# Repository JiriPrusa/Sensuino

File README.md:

Sensuino
========

Welcome on Sensuino project repository!

Here you can find schemats for Sensuino shield, EC modul and pH modul in folder Schema. Also the Arduino code for Sensunino shield and relevant libraries are placed here in folder Arduino. And at last source code in JAVA for SensApl application is situated in folder SensApl.

=======

More information about project can be found on project page : http://sensuino.net

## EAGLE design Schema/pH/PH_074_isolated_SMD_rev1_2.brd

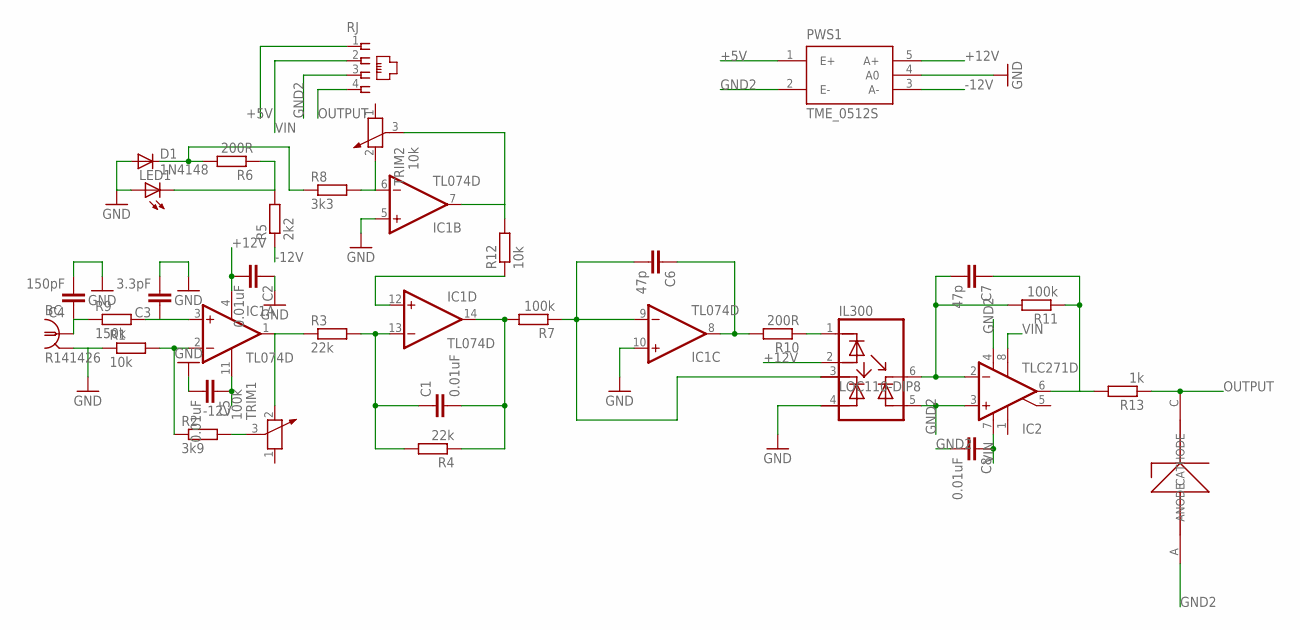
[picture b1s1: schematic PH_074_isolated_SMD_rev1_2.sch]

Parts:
BC: R141426
C1, C2: 0.01uF; C1206
C3: 3.3pF; C0805
C4: 150pF; C0805
C5, C8: 0.01uF; C0805
C6: 47p; C0805
C7: 47p; C1206
D1: 1N4148; R1206W
IC1: TL074D; SO14
IC2: TLC271D; SO08
IL300: LOC110-DIP8; DIP8
LED1: LED3MM
PWS1: TME_0512S; TMEXXXXS
R1, R12: 10k; R1206W
R2: 3k9; R1206W
R3, R4: 22k; R1206W
R5: 2k2; R1206W
R6, R10: 200R; R1206W
R7, R11: 100k; R1206W
R8: 3k3; R1206W
R9: 150k; R0805W
R13: 1k; R1206W
RJ: 14867
TRIM1: 100k; PT-10
TRIM2: 10k; PT-10
U$1: ZENER; SOD80-W

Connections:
+5V: PWS1.1 (E+), RJ.1
+12V: C2.2, IC1.4 (V+), IL300.2, PWS1.5 (A+)
-12V: C5.1, IC1.11 (V-), PWS1.3 (A-), R5.1
GND: BC.2 (GND), BC.3 (GND), BC.4 (GND), BC.5 (GND), C2.1, C3.2, C4.2, C5.2, D1.1 (A), IC1.5 (+IN), IC1.10 (+IN), IL300.4, LED1.A, PWS1.4 (A0), R1.1
GND2: C8.2, IC2.3 (+IN), IC2.4 (V-), IL300.5, PWS1.2 (E-), RJ.3, U$1.A (ANODE)
IN: C1.2, IC1.14 (OUT), R4.1, R7.2
unnamed: IC1.6 (-IN), R8.2, TRIM2.2
unnamed: IC1.2 (-IN), R1.2, R2.1
unnamed: C3.1, IC1.3 (+IN), R9.2
unnamed: C6.2, IC1.9 (-IN), IL300.3, R7.1
unnamed: R2.2, TRIM1.3
unnamed: BC.1, C4.1, R9.1
unnamed: D1.2 (C), R6.2, R8.1
unnamed: LED1.K (C), R5.2, R6.1
unnamed: IL300.1, R10.1
unnamed: IC1.7 (OUT), R12.2, TRIM2.3
unnamed: IC1.1 (OUT), R3.1, TRIM1.2
unnamed: C6.1, IC1.8 (OUT), R10.2
unnamed: IC1.12 (+IN), R12.1
unnamed: C1.1, IC1.13 (-IN), R3.2, R4.2
unnamed: C7.2, IC2.2 (-IN), IL300.6, R11.2
NIC: C7.1, IC2.6 (OUT), R11.1, R13.2
OUTPUT: R13.1, RJ.4, U$1.C (CATHODE)
VIN: C8.1, IC2.7 (V+), IC2.8 (OPT), RJ.2

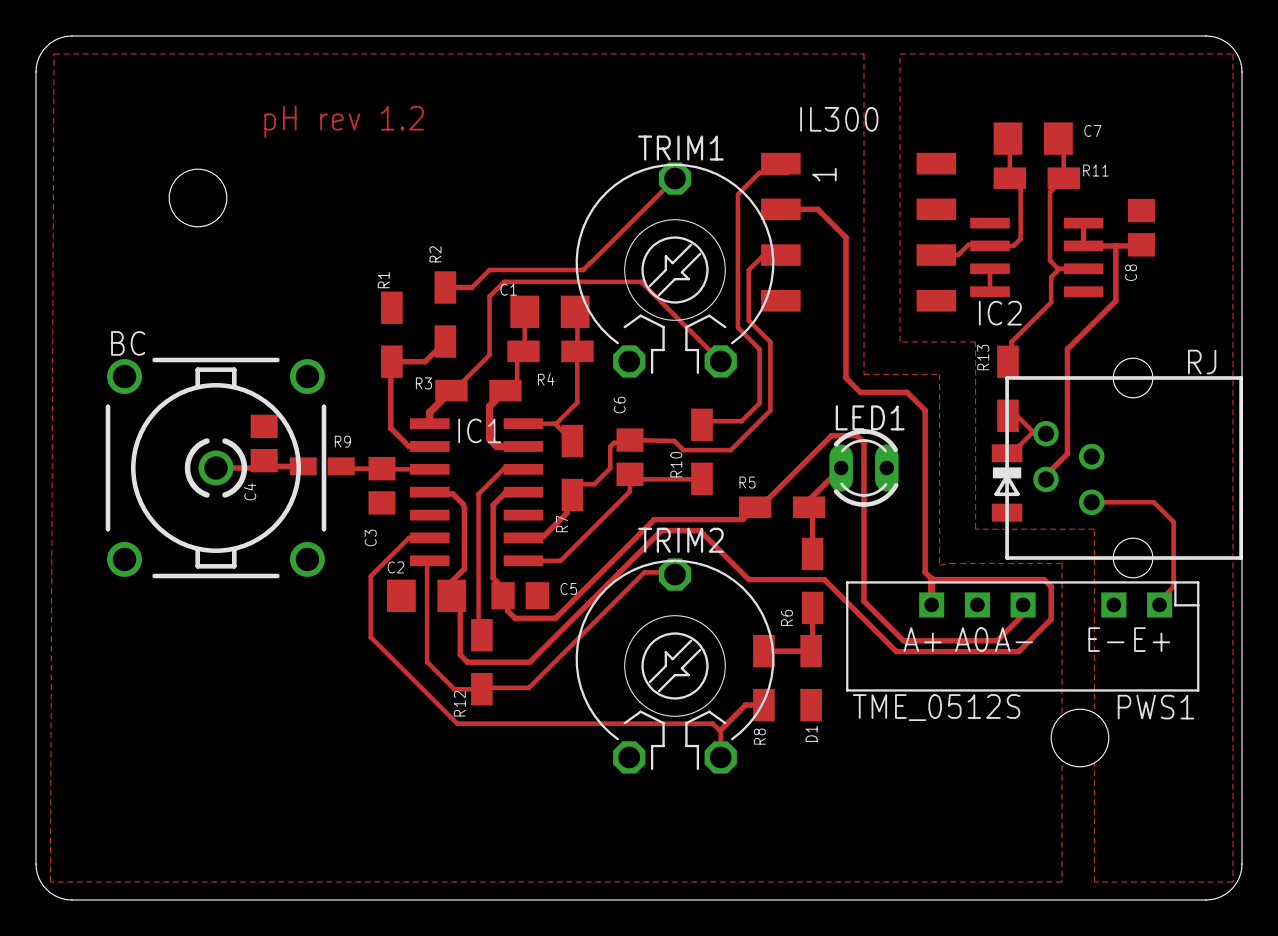
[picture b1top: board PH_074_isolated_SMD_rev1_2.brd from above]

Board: 2 copper layers, 67.0 x 48.0 mm, 32 parts (0 on the bottom side), 24 nets.

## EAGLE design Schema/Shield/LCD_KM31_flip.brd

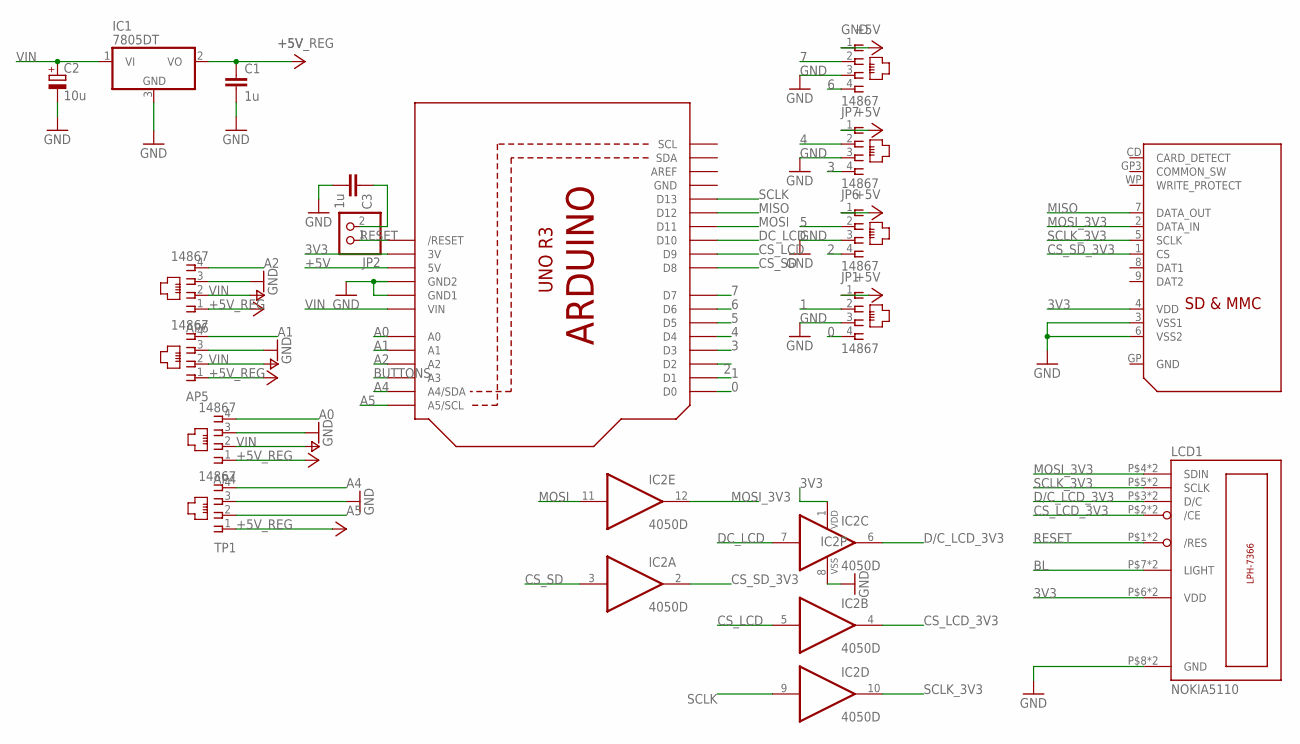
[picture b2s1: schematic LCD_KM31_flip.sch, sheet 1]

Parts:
AP4, AP5, AP6: 14867
C1, C3: 1u; C1206
C2: 10u; SMC_C
GND: 14867
IC1: 7805DT; TO252
IC2: 4050D; SO16
JP1, JP6, JP7: 14867
JP2: PINHD-1X2; 1X02
LCD1: NOKIA5110; LPH-7366
TP1: 14867
U$1: ARDUINOR3-NOIOREF-NOTEXT; ARDUINOR3-NOTEXT-NOIOREF
U$2: SDMMC06132; 06132

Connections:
0: JP1.4, U$1.D0
1: JP1.2, U$1.D1
2: JP6.4, U$1.D2
3: JP7.4, U$1.D3
3V3: IC2.1 (VDD), LCD1.P$6 (VDD), LCD1.P$14 (VDD), U$1.3V, U$2.4 (VDD)
4: JP7.2, U$1.D4
5: JP6.2, U$1.D5
6: GND.4, U$1.D6
7: GND.2, U$1.D7
+5V: GND.1, JP1.1, JP6.1, JP7.1, U$1.5V; also elsewhere on the board
+5V_REG: AP4.1, AP5.1, AP6.1, C1.1, IC1.2 (VO), TP1.1
A0: AP4.4, U$1.A0
A1: AP5.4, U$1.A1
A2: AP6.4, U$1.A2
A4: TP1.4, U$1.A4 (A4/SDA)
A5: TP1.2, U$1.A5 (A5/SCL)
BL: LCD1.P$7 (LIGHT), LCD1.P$15 (LIGHT); also elsewhere on the board
BUTTONS: U$1.A3; also elsewhere on the board
CS_LCD: IC2.5 (I), U$1.D9
CS_LCD_3V3: IC2.4 (O), LCD1.P$2 (/CE), LCD1.P$10 (/CE)
CS_SD: IC2.3 (I), U$1.D8
CS_SD_3V3: IC2.2 (O), U$2.1 (CS)
D/C_LCD_3V3: IC2.6 (O), LCD1.P$3 (D/C), LCD1.P$11 (D/C)
DC_LCD: IC2.7 (I), U$1.D10
GND: AP4.3, AP5.3, AP6.3, C1.2, C2.-, C3.2, GND.3, IC1.3 (GND), IC2.8 (VSS), JP1.3, JP6.3, JP7.3, LCD1.P$8 (GND), LCD1.P$16 (GND), TP1.3, U$1.GND, U$1.GND1, U$1.GND2, U$2.3 (VSS1), U$2.6 (VSS2); also elsewhere on the board
MISO: U$1.D12, U$2.7 (DATA_OUT)
MOSI: IC2.11 (I), U$1.D11
MOSI_3V3: IC2.12 (O), LCD1.P$4 (SDIN), LCD1.P$12 (SDIN), U$2.2 (DATA_IN)
unnamed: C3.1, JP2.2
RESET: JP2.1, LCD1.P$1 (/RES), LCD1.P$9 (/RES), U$1.RESET (/RESET)
SCLK: IC2.9 (I), U$1.D13
SCLK_3V3: IC2.10 (O), LCD1.P$5 (SCLK), LCD1.P$13 (SCLK), U$2.5 (SCLK)
VIN: AP4.2, AP5.2, AP6.2, C2.+, IC1.1 (VI), U$1.VIN

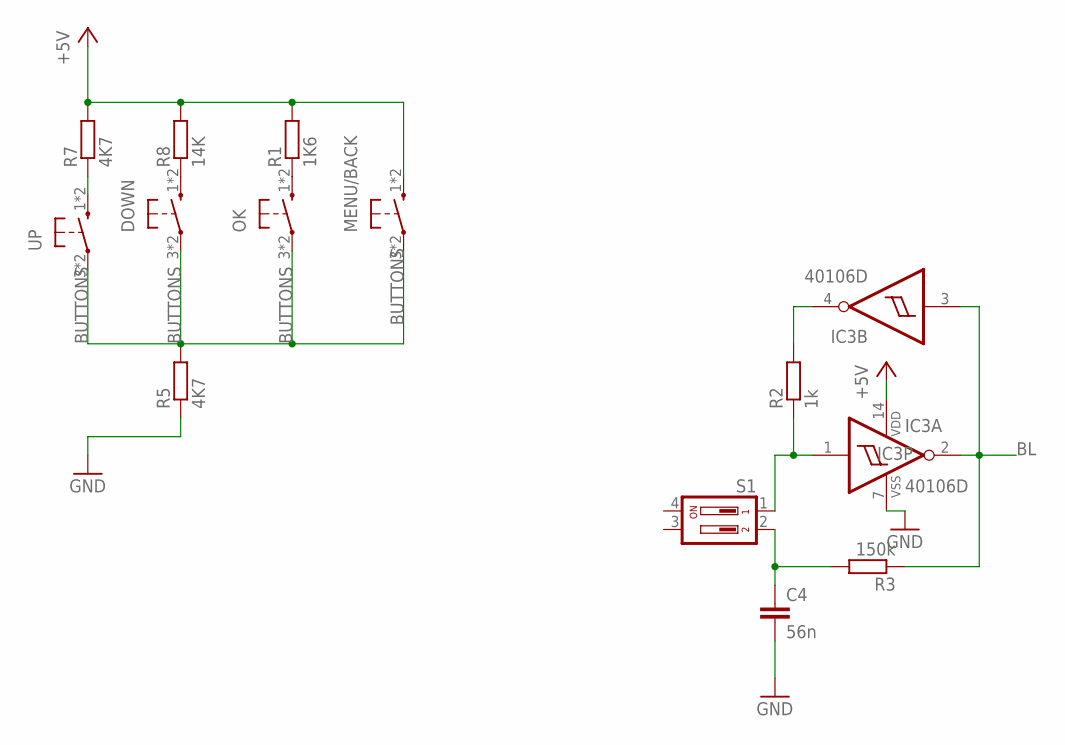
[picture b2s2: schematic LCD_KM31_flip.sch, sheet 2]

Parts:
C4: 56n; C0805
DOWN: 10-XX; B3F-10XX
IC3: 40106D; SO14
MENU/BACK: 10-XX; B3F-10XX
OK: 10-XX; B3F-10XX
R1: 1K6; M0805
R2: 1k; R0805W
R3: 150k; R0805W
R5, R7: 4K7; M0805
R8: 14K; M0805
S1: SD4-02
UP: 10-XX; B3F-10XX

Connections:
+5V: IC3.14 (VDD), MENU/BACK.1 (S), MENU/BACK.2 (S), R1.2, R7.2, R8.2; also elsewhere on the board
BL: IC3.2 (O), IC3.3 (I), R3.1; also elsewhere on the board
BUTTONS: DOWN.3, DOWN.4, MENU/BACK.3, MENU/BACK.4, OK.3, OK.4, R5.2, UP.3, UP.4; also elsewhere on the board
GND: C4.2, IC3.7 (VSS), R5.1; also elsewhere on the board
unnamed: DOWN.1 (S), DOWN.2 (S), R8.1
unnamed: OK.1 (S), OK.2 (S), R1.1
unnamed: R7.1, UP.1 (S), UP.2 (S)
unnamed: C4.1, R3.2, S1.2
unnamed: IC3.1 (I), R2.1, S1.1
unnamed: IC3.4 (O), R2.2

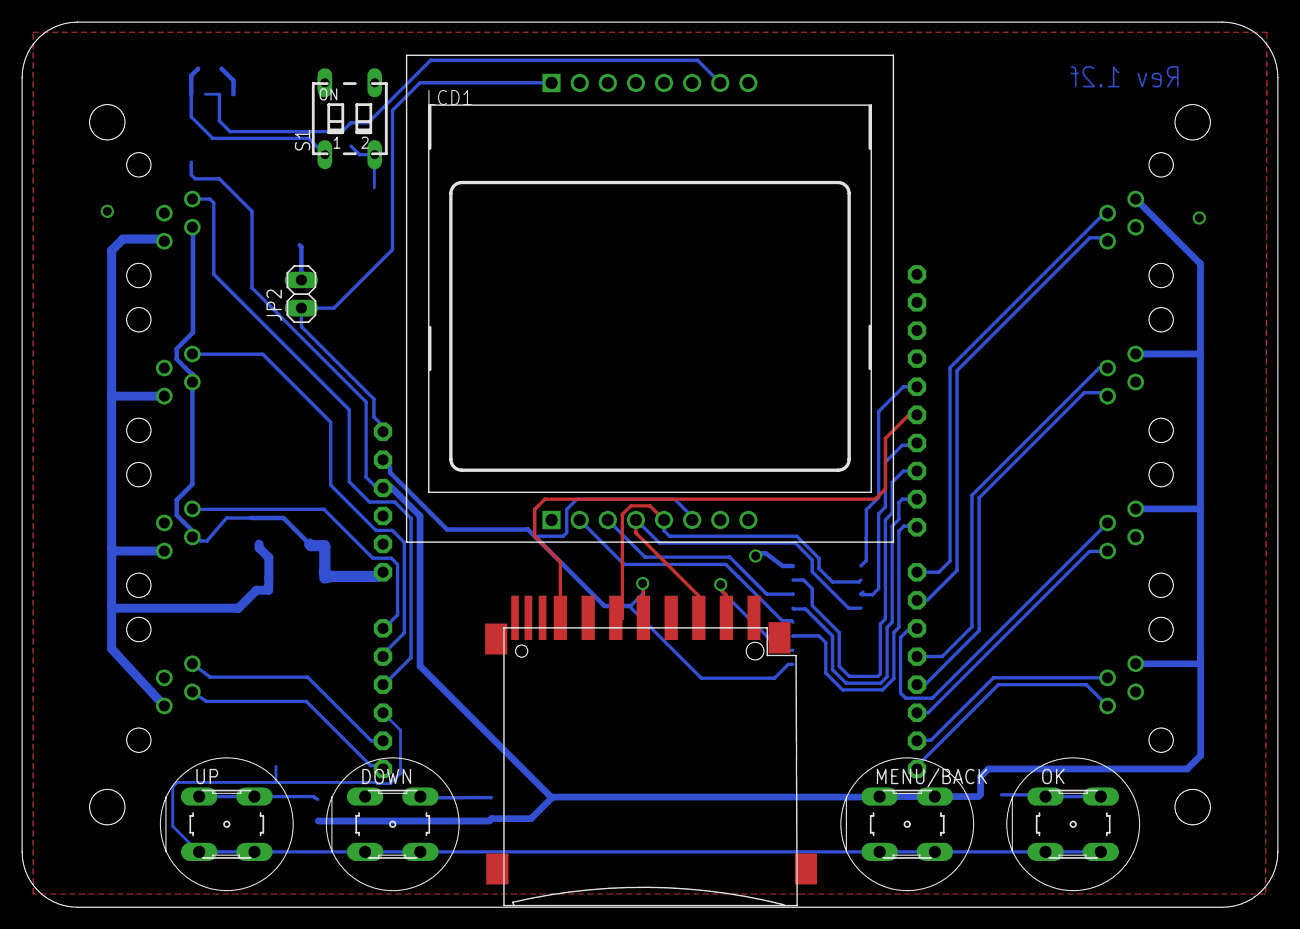
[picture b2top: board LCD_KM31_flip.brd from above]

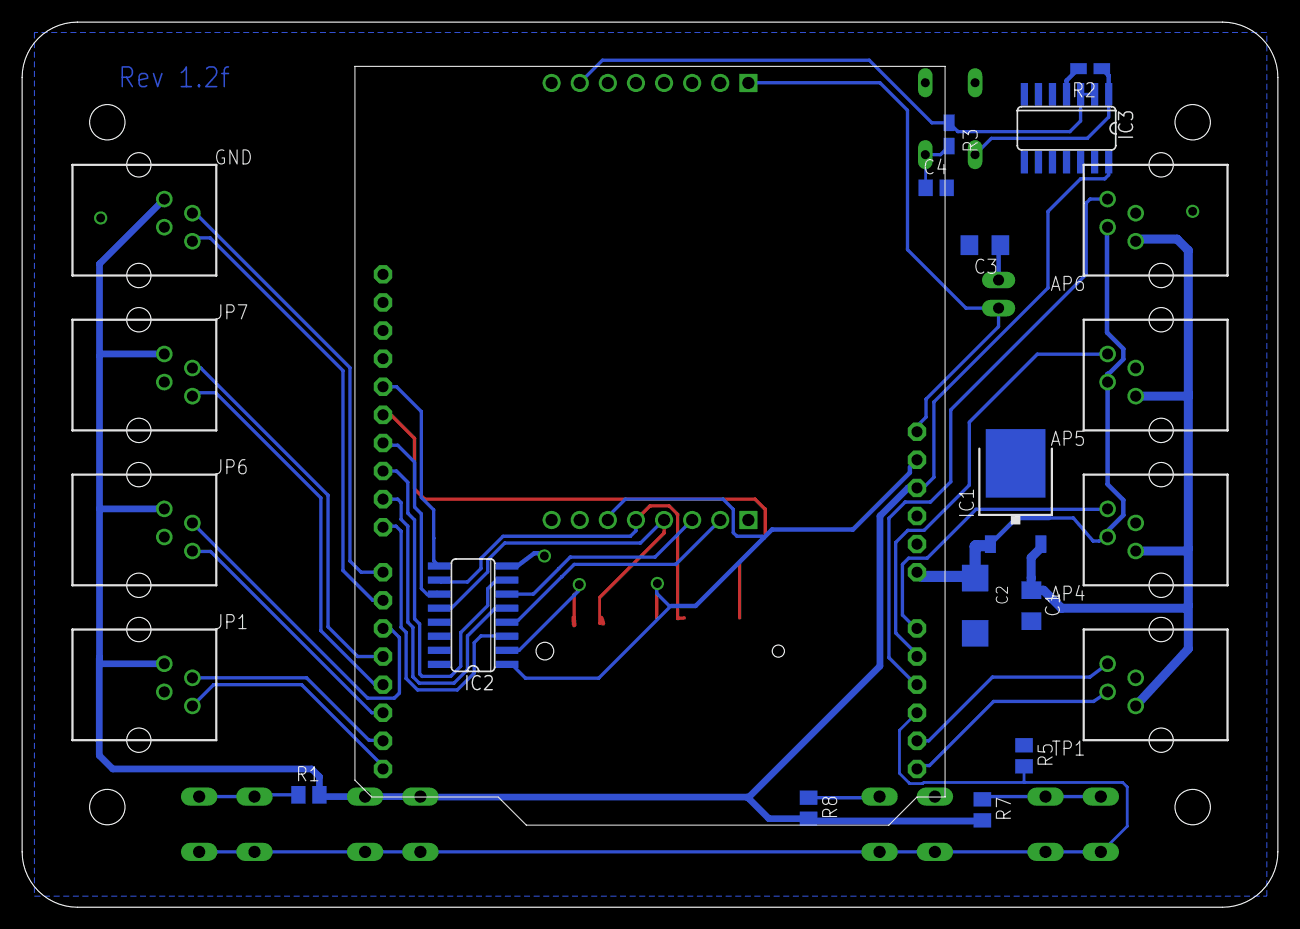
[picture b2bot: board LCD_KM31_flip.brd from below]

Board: 2 copper layers, 113.5 x 80.0 mm, 30 parts (21 on the bottom side), 39 nets.

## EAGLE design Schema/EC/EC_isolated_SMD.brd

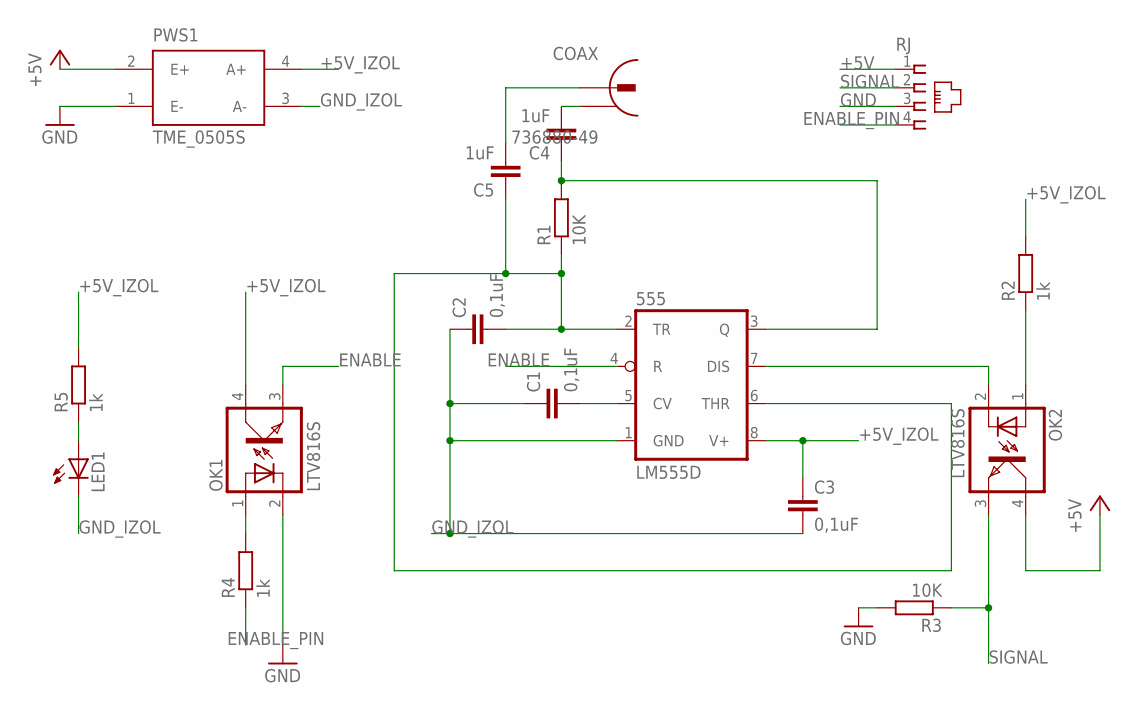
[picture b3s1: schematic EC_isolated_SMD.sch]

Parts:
555: LM555D; SO08
C1, C2, C3: 0,1uF; C1206
C4, C5: 1uF; C1206
COAX: 736880-49
LED1: LEDLZR181; LZR181
OK1, OK2: LTV816S; SMD4
PWS1: TME_0505S; TMEXXXXS
R1: 10K; R1206W
R2, R4: 1k; R1206W
R3: 10K; R0805W
R5: 1k; R0805W
RJ: 14867

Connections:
+5V: OK2.4 (COL), PWS1.2 (E+), RJ.1
+5V_IZOL: 555.8 (V+), C3.1, OK1.4 (COL), PWS1.4 (A+), R2.2, R5.2
ENABLE: 555.4 (R), OK1.3 (EMIT)
ENABLE_PIN: R4.1, RJ.4
GND: OK1.2 (C), PWS1.1 (E-), R3.2, RJ.3
GND_IZOL: 555.1 (GND), C1.1, C2.1, C3.2, LED1.K (C), PWS1.3 (A-)
unnamed: 555.3 (Q), C4.1, R1.2
unnamed: OK2.1 (A), R2.1
unnamed: 555.2 (TR), 555.6 (THR), C2.2, C5.1, R1.1
unnamed: C4.2, COAX.2
unnamed: 555.5 (CV), C1.2
unnamed: LED1.A, R5.1
unnamed: 555.7 (DIS), OK2.2 (C)
unnamed: OK1.1 (A), R4.2
unnamed: C5.2, COAX.1
SIGNAL: OK2.3 (EMIT), R3.1, RJ.2

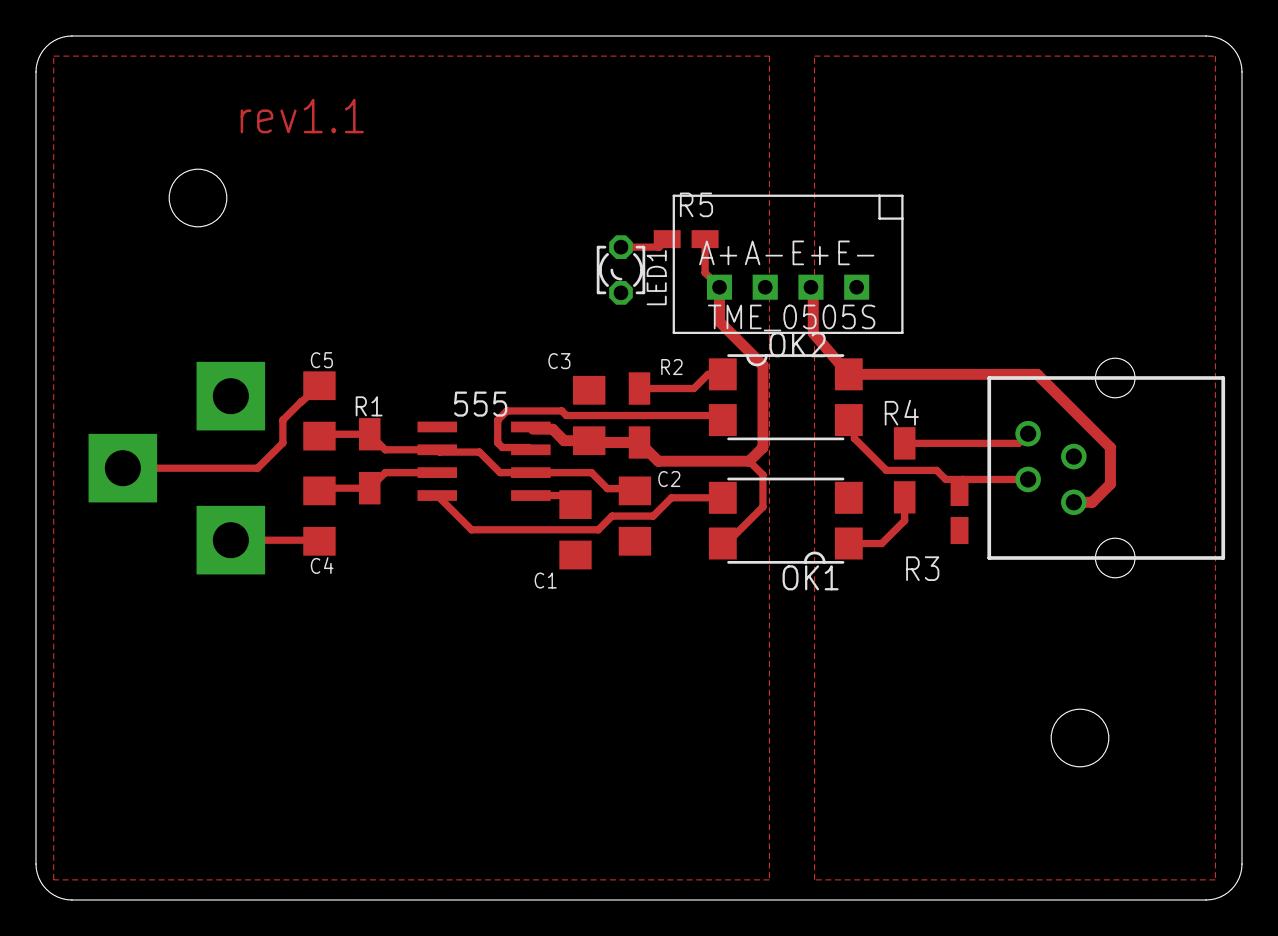
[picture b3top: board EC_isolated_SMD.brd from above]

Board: 2 copper layers, 67.0 x 48.0 mm, 17 parts (1 on the bottom side), 16 nets.

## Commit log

2014-05-21 Add arduino sketches
2014-05-21 necessary libraries add
2014-05-22 Add EC schema
2014-06-05 Add pH schema
2014-06-08 update pH schema and board
2014-06-10 little board adjustment
2014-06-27 C3 and C4 corrected values
2014-08-11 actualization
2014-08-11 add Sensapl
2014-08-11 add Shield
2014-11-20 change _maxEchoTime in ECRead()
2014-11-20 schema upload
2014-11-22 Split main sketch to more files for better readability
